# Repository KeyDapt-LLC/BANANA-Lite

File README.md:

# BANANA-Lite

BANANA-Lite is a modified version of the [BANANA keyboard by RGBKB](https://github.com/RGBKB/Keyboard-files/tree/main/BANANA).

**Get one at [keydapt.com/products/banana-keyboard](https://keydapt.com/products/banana-keyboard).**

## Changes from the original

- **Nav switch removed:** the TM-2028 nav switch and its CNC hat are gone.
- **RGB removed:** the 48 per-key LEDs and 6 underglow LEDs are gone.
- **Magnets:** the case and stand use 9 × 1/4" magnets instead of the original's 11 × 6 mm × 6 mm magnets.

> **Note:** Only `10133.kicad_pcb` was modified. `10133.kicad_sch` is unchanged from the original and still shows the nav switch and RGB components.
## Instructions
Please view the original project for print and build instructions. They are the same.

## License

GPL-3.0, the same license as the original [RGBKB Keyboard-files](https://github.com/RGBKB/Keyboard-files).

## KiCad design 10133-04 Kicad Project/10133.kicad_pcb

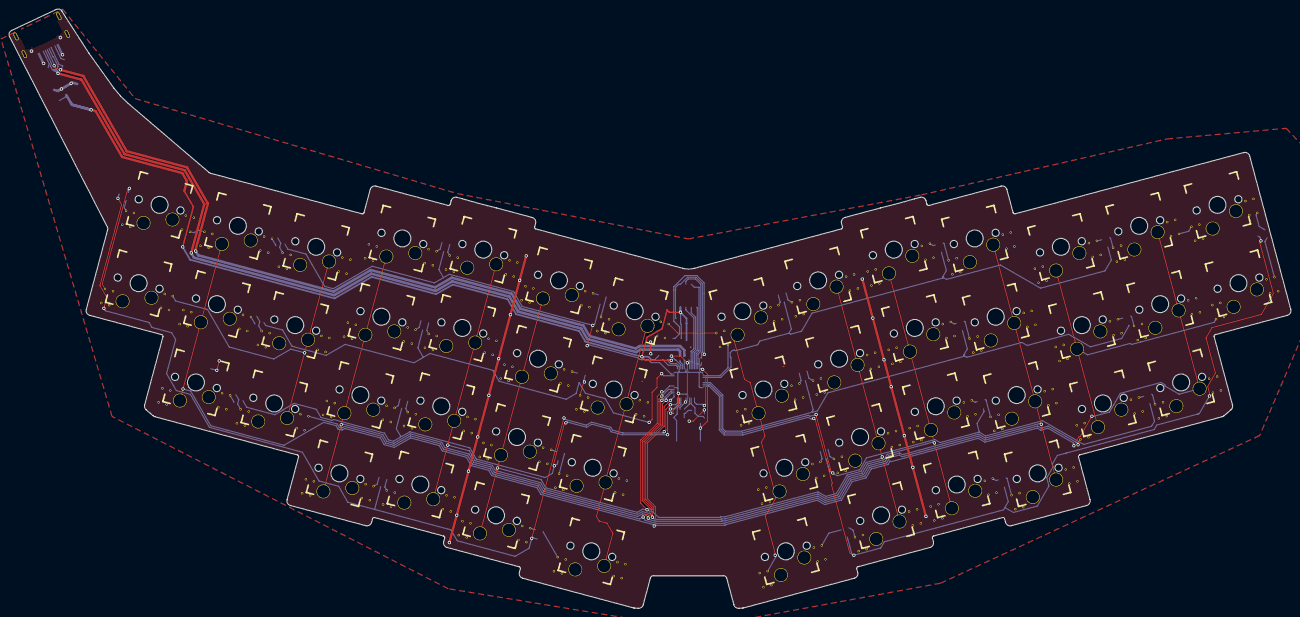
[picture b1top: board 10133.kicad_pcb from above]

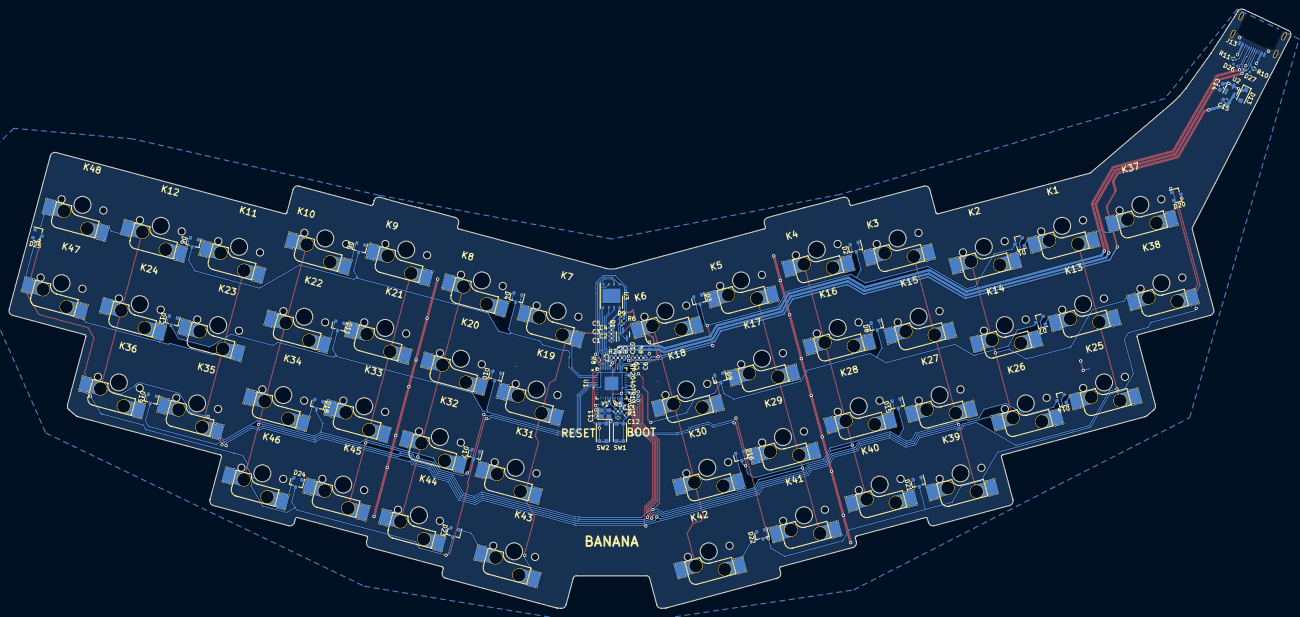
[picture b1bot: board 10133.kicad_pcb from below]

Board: 2 copper layers, 301.2 x 140.8 mm, 108 parts (108 on the bottom side), 85 nets.

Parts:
C1, C2, C3, C4, C5, C6: 100nF; C_0402_1005Metric
C7, C8, C9, C10, C13: 2.2uF; C_0402_1005Metric
C11, C12: 15pF; C_0402_1005Metric
C14, C15: 100nF; C_0603_1608Metric
D1, D2, D3, D4, D5, D6, D7, D8, D9, D10, D11, D12, D14, D15, D16, D17, D18, D19, D20, D21, D22, D23, D24, D25: LBAV170LT1G; SOT-23-minimal
D13: 1N4007; D_SOD-123F
D26, D27: GG0402052R542P; D_0402_1005Metric
J13: USB_C_Receptacle_USB2.0; HRO-TYPE-C-31-M-14
K1, K2, K3, K4, K5, K6, K7, K8, K9, K10, K11, K12, K13, K14, K15, K16, K17, K18, K19, K20, K21, K22, K23, K24, K25, K26, K27, K28, K29, K30, K31, K32, K33, K34, K35, K36, K37, K38, K39, K40, K41, K42, K43, K44, K45, K46, K47, K48: KEYSW; MX-Kailh-Socket
Q1: BSS138; SOT-23
R1, R9: 10kR; R_0402_1005Metric
R2, R3: 27R; R_0402_1005Metric
R4: 200R; R_0402_1005Metric
R5, R8: 1kR; R_0402_1005Metric
R6: 7.15kR; R_0402_1005Metric
R10, R11: 5.1kR; R_0402_1005Metric
SW1, SW2: KMR221NGLFS; SW_Push_1P1T_NO_CK_KMR2
U1: RP2040TR13
U2: MCP1700-3302E_SOT23; SOT-23
U3: W25Q32JVZP; WSON-8-1EP_6x5mm_P1.27mm_EP3.4x4.3mm
Y1: 12Mhz; Crystal_SMD_2520-4Pin_2.5x2.0mm

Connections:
+1V1: C7.1, C8.1, C13.1, U1.23 (DVDD), U1.45 (VREG_VOUT), U1.50 (DVDD)
+3V3: C1.1, C2.1, C3.1, C4.1, C5.1, C6.1, C10.1, C15.1, D13.2 (A), Q1.1 (G), R1.1, R4.1, R6.2, R9.1, U1.1 (IOVDD), U1.10 (IOVDD), U1.22 (IOVDD), U1.33 (IOVDD), U1.42 (IOVDD), U1.44 (VREG_VIN), U1.48 (USB_VDD), U1.49 (IOVDD), U2.2 (VO), U3.8 (VCC)
+5V: C14.2, D13.1 (K), J13.A4 (VBUS), J13.A9 (VBUS), J13.B4 (VBUS), J13.B9 (VBUS), U2.3 (VI)
/BOOT: R8.1, SW2.2, U1.56 (QSPI_SCN)
/CLK: U1.52 (QSPI_SCLK), U3.6 (CLK)
/CS: R8.2, R9.2, U3.1 (~CS)
/D+: D26.1 (K), J13.A6 (D+), J13.B6 (D+), R2.1
/D-: D27.1 (K), J13.A7 (D-), J13.B7 (D-), R3.1
/RESET: R1.2, SW1.2, U1.26 (RUN)
/RGB_3.3v: Q1.2 (S), R6.1, U1.18 (GPIO15)
/SPI-0: U1.53 (QSPI_SD0), U3.5 (DI(IO0))
/SPI-1: U1.55 (QSPI_SD1), U3.2 (DO(IO1))
/SPI-2: U1.54 (QSPI_SD2), U3.3 (IO2)
/SPI-3: U1.51 (QSPI_SD3), U3.7 (IO3)
/c0: K1.2, K12.1, K13.2, K24.1, K25.2, K36.1, K37.1, K48.2, U1.29 (GPIO18)
/c1: K2.1, K11.2, K14.1, K23.2, K26.1, K35.2, K38.1, K47.2, U1.32 (GPIO21)
/c2: K3.2, K10.1, K15.2, K22.1, K27.2, K34.1, K39.2, K46.1, U1.31 (GPIO20)
/c3: K4.1, K9.2, K16.1, K21.2, K28.1, K33.2, K40.1, K45.2, U1.30 (GPIO19)
/c4: K5.2, K8.1, K17.2, K20.1, K29.2, K32.1, K41.2, K44.1, U1.34 (GPIO22)
/c5: K6.1, K7.2, K18.1, K19.2, K30.1, K31.2, K42.1, K43.2, U1.3 (GPIO1)
/k37: D20.2 (A), K37.2
/k38: D20.1 (A), K38.2
/k47: D25.2 (A), K47.1
/k48: D25.1 (A), K48.1
/r0: D1.3 (C), D2.3 (C), D3.3 (C), U1.41 (GPIO29/ADC3)
/r1: D7.3 (C), D8.3 (C), D9.3 (C), U1.40 (GPIO28/ADC2)
/r2: D14.3 (C), D15.3 (C), D16.3 (C), U1.27 (GPIO16)
/r3: D20.3 (C), D21.3 (C), D22.3 (C), U1.28 (GPIO17)
/r4: D4.3 (C), D5.3 (C), D6.3 (C), U1.4 (GPIO2)
/r5: D10.3 (C), D11.3 (C), D12.3 (C), U1.7 (GPIO5)
/r6: D17.3 (C), D18.3 (C), D19.3 (C), U1.8 (GPIO6)
/r7: D23.3 (C), D24.3 (C), D25.3 (C), U1.9 (GPIO7)
GND: C1.2, C2.2, C3.2, C4.2, C5.2, C6.2, C7.2, C8.2, C9.2, C10.2, C11.2, C12.1, C13.2, C14.1, C15.2, D26.2 (A), D27.2 (A), J13.A1 (GND), J13.A12 (GND), J13.B1 (GND), J13.B12 (GND), J13.S1 (SHIELD), R10.2, R11.2, SW1.1, SW2.1, U1.19 (TESTEN), U1.57 (GND), U2.1 (GND), U3.4 (GND), Y1.2, Y1.4
unnamed: C12.2, R5.2, Y1.3
unnamed: D1.1 (A), K1.1
unnamed: D1.2 (A), K2.2
unnamed: D2.1 (A), K3.1
unnamed: D2.2 (A), K4.2
unnamed: D3.1 (A), K5.1
unnamed: D3.2 (A), K6.2
unnamed: D4.1 (A), K7.1
unnamed: D4.2 (A), K8.2
unnamed: D5.1 (A), K9.1
unnamed: D5.2 (A), K10.2
unnamed: D6.1 (A), K11.1
unnamed: D6.2 (A), K12.2
unnamed: D7.1 (A), K13.1
unnamed: D7.2 (A), K14.2
unnamed: D8.1 (A), K15.1
unnamed: D8.2 (A), K16.2
unnamed: D9.1 (A), K17.1
unnamed: D9.2 (A), K18.2
unnamed: D10.1 (A), K19.1
unnamed: D10.2 (A), K20.2
unnamed: D11.1 (A), K21.1
unnamed: D11.2 (A), K22.2
unnamed: D12.1 (A), K23.1
unnamed: D12.2 (A), K24.2
unnamed: D14.1 (A), K25.1
unnamed: D14.2 (A), K26.2
unnamed: D15.1 (A), K27.1
unnamed: D15.2 (A), K28.2
unnamed: D16.1 (A), K29.1
unnamed: D16.2 (A), K30.2
unnamed: D17.1 (A), K31.1
unnamed: D17.2 (A), K32.2
unnamed: D18.1 (A), K33.1
unnamed: D18.2 (A), K34.2
unnamed: D19.1 (A), K35.1
unnamed: D19.2 (A), K36.2
unnamed: D21.1 (A), K39.1
unnamed: D21.2 (A), K40.2
unnamed: D22.1 (A), K41.1
unnamed: D22.2 (A), K42.2
unnamed: D23.1 (A), K43.1
unnamed: D23.2 (A), K44.2
unnamed: D24.1 (A), K45.1
unnamed: D24.2 (A), K46.2
unnamed: J13.A5 (CC1), R10.1
unnamed: J13.B5 (CC2), R11.1
unnamed: C9.1, R4.2, U1.43 (ADC_AVDD)
unnamed: R3.2, U1.46 (USB_DM)
unnamed: R2.2, U1.47 (USB_DP)
unnamed: C11.1, U1.20 (XIN), Y1.1
unnamed: R5.1, U1.21 (XOUT)

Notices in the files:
parts and their libraries:
Copyright 2021 Accelerated Designs. All rights reserved.
